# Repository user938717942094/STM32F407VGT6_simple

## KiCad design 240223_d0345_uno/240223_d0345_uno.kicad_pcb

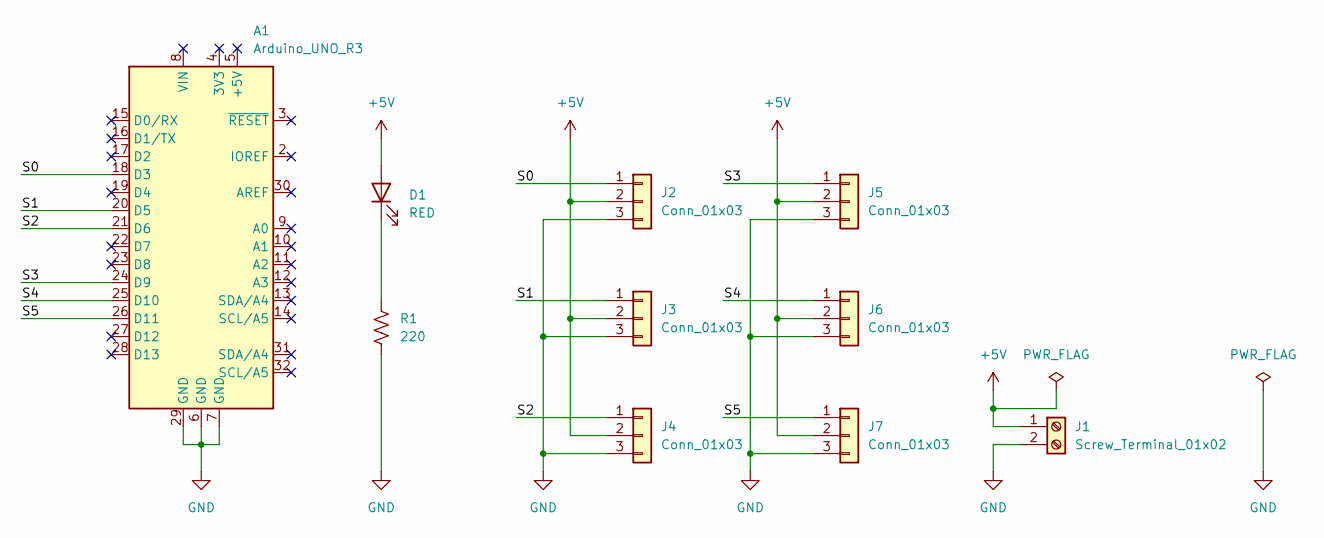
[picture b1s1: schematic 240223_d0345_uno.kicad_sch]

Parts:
A1: Arduino_UNO_R3
D1: RED; LED_D5.0mm
J1: Screw_Terminal_01x02; TerminalBlock_Phoenix_MKDS-1,5-2_1x02_P5.00mm_Horizontal
J2, J3, J4, J5, J6, J7: Conn_01x03; PinHeader_1x03_P2.54mm_Vertical
R1: 220; C_Disc_D5.0mm_W2.5mm_P5.00mm

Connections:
+5V: D1.2 (A), J1.1, J2.2, J3.2, J4.2, J5.2, J6.2, J7.2
/S0: A1.18 (D3), J2.1
/S1: A1.20 (D5), J3.1
/S2: A1.21 (D6), J4.1
/S3: A1.24 (D9), J5.1
/S4: A1.25 (D10), J6.1
/S5: A1.26 (D11), J7.1
GND: A1.6 (GND), A1.7 (GND), A1.29 (GND), J1.2, J2.3, J3.3, J4.3, J5.3, J6.3, J7.3, R1.2
unnamed: D1.1 (K), R1.1

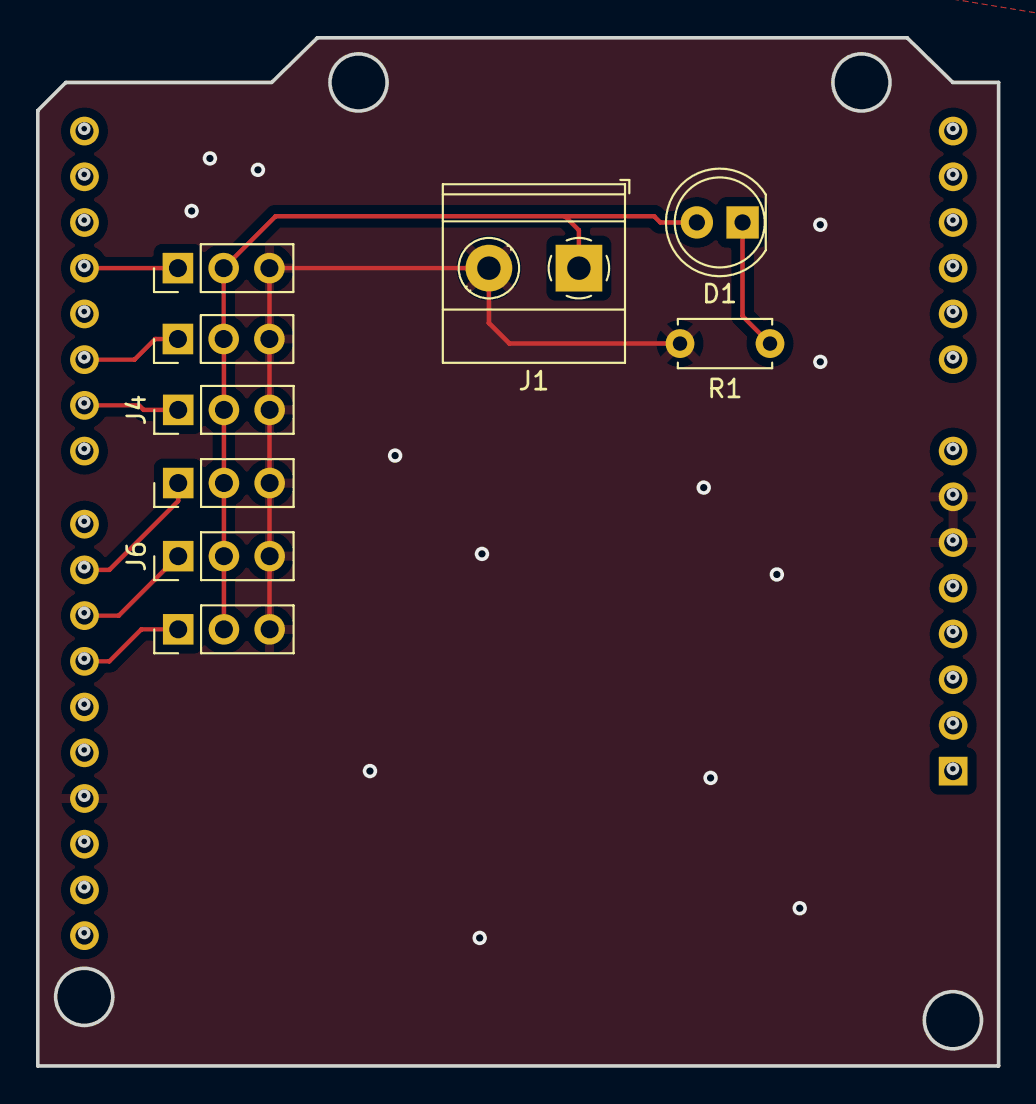
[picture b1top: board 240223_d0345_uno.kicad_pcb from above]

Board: 2 copper layers, 53.4 x 57.1 mm, 10 parts (1 on the bottom side), 9 nets.

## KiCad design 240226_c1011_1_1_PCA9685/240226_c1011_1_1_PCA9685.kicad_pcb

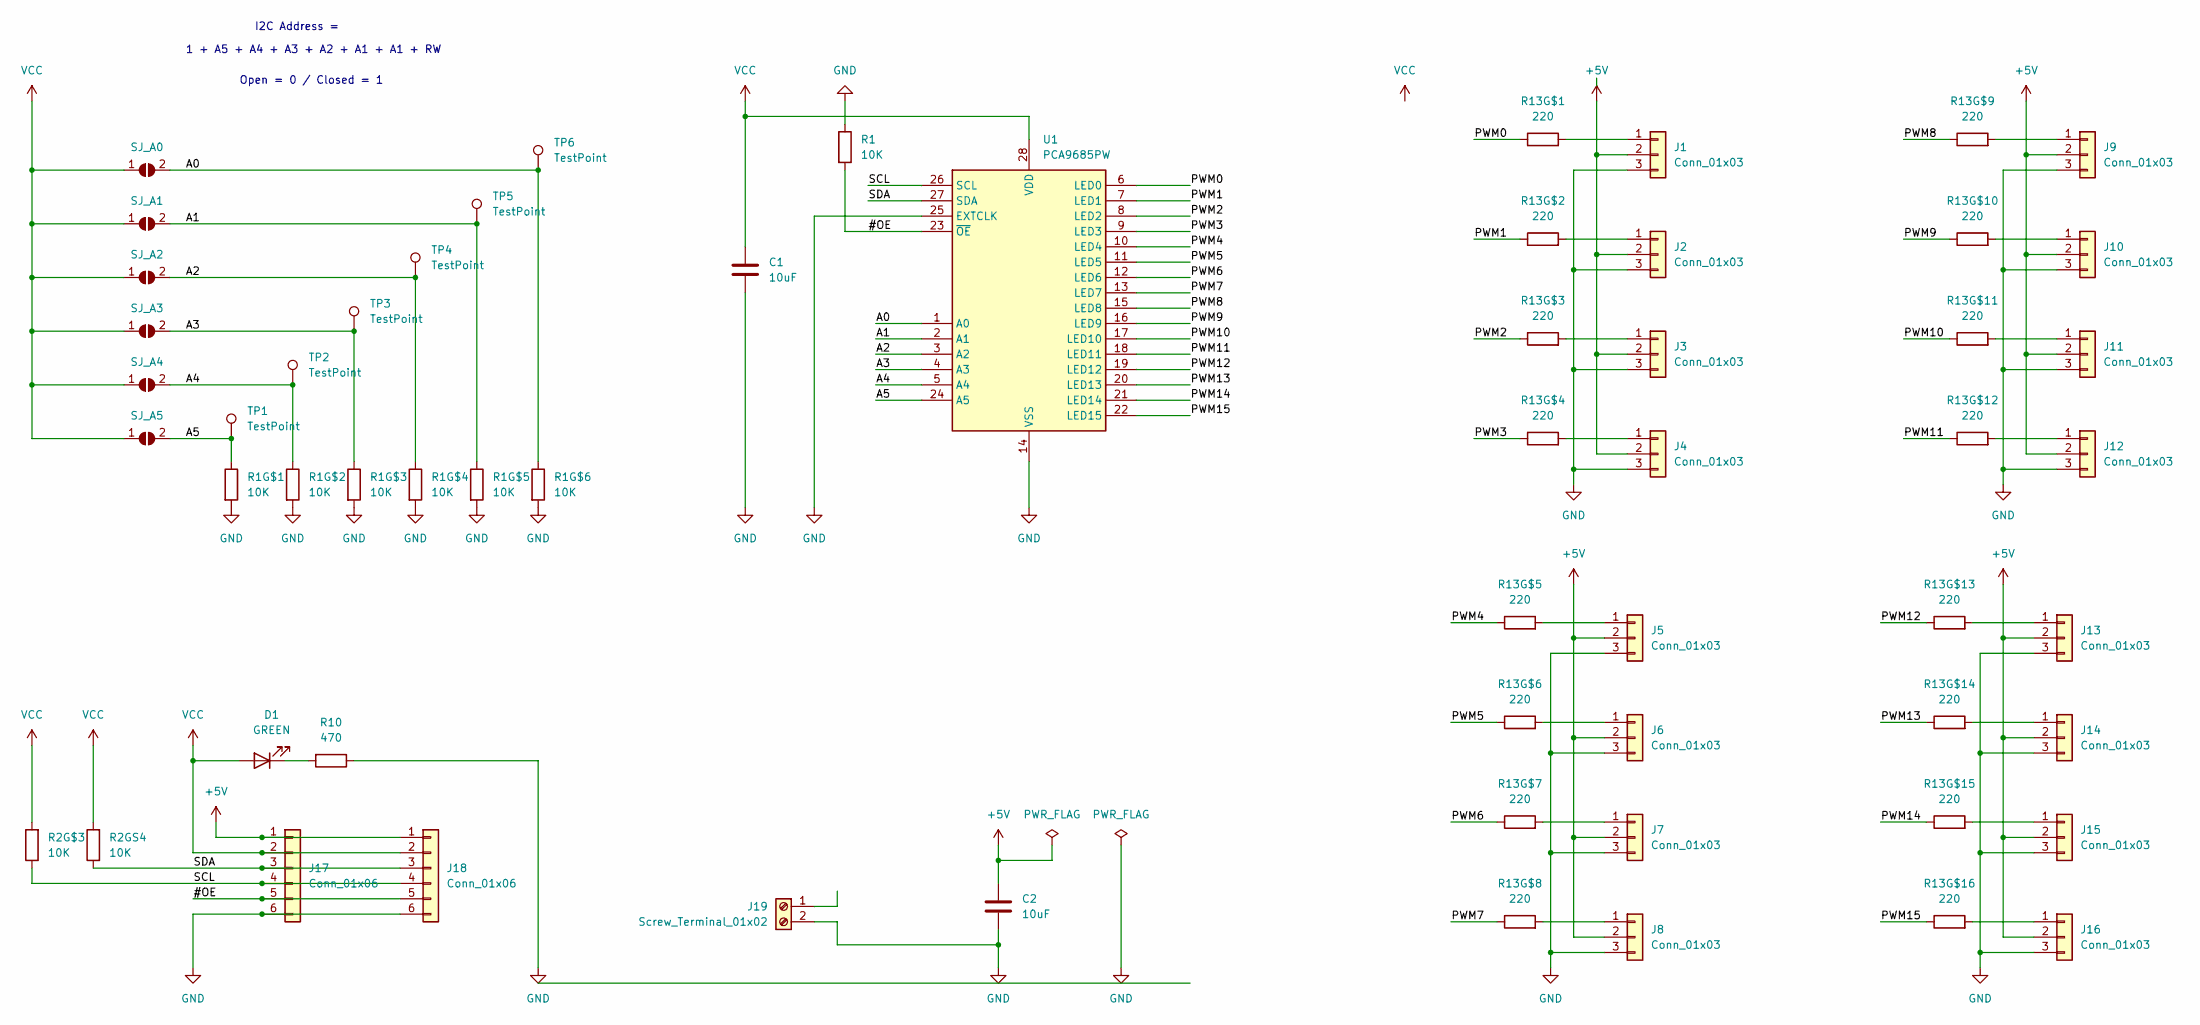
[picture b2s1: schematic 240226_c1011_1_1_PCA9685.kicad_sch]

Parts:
C1, C2: 10uF
D1: GREEN
J1, J2, J3, J4, J5, J6, J7, J8, J9, J10, J11, J12, J13, J14, J15, J16: Conn_01x03; PinHeader_1x03_P2.54mm_Vertical
J17, J18: Conn_01x06
J19: Screw_Terminal_01x02; TerminalBlock_Phoenix_MKDS-1,5-2_1x02_P5.00mm_Horizontal
JP1: SJ_A0
JP2: SJ_A1
JP3: SJ_A2
JP4: SJ_A3
JP5: SJ_A4
JP6: SJ_A5
R1, R1G$1, R1G$2, R1G$3, R1G$4, R1G$5, R1G$6, R2G$3, R2GS4: 10K
R10: 470
R13G$1, R13G$2, R13G$3, R13G$4, R13G$5, R13G$6, R13G$7, R13G$8, R13G$9, R13G$10, R13G$11, R13G$12, R13G$13, R13G$14, R13G$15, R13G$16: 220
TP1, TP2, TP3, TP4, TP5, TP6: TestPoint
U1: PCA9685PW; TSSOP-28_4.4x9.7mm_P0.65mm

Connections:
+5V: C2.1, J1.2, J2.2, J3.2, J4.2, J5.2, J6.2, J7.2, J8.2, J9.2, J10.2, J11.2, J12.2, J13.2, J14.2, J15.2, J16.2, J17.1, J18.1; also elsewhere on the board
/#OE: J17.5, J18.5, R1.2, U1.23 (~OE)
/A0: JP1.2 (B), R1G$6.1, TP6.1, U1.1 (A0); also elsewhere on the board
/A1: JP2.2 (B), R1G$5.1, TP5.1, U1.2 (A1); also elsewhere on the board
/A2: JP3.2 (B), R1G$4.1, TP4.1, U1.3 (A2); also elsewhere on the board
/A3: JP4.2 (B), R1G$3.1, TP3.1, U1.4 (A3); also elsewhere on the board
/A4: JP5.2 (B), R1G$2.1, TP2.1, U1.5 (A4); also elsewhere on the board
/A5: JP6.2 (B), R1G$1.1, TP1.1, U1.24 (A5); also elsewhere on the board
/PWM0: R13G$1.1, U1.6 (LED0)
/PWM1: R13G$2.1, U1.7 (LED1)
/PWM2: R13G$3.1, U1.8 (LED2)
/PWM3: R13G$4.1, U1.9 (LED3)
/PWM4: R13G$5.1, U1.10 (LED4)
/PWM5: R13G$6.1, U1.11 (LED5)
/PWM6: R13G$7.1, U1.12 (LED6)
/PWM7: R13G$8.1, U1.13 (LED7)
/PWM8: R13G$9.1, U1.15 (LED8)
/PWM9: R13G$10.1, U1.16 (LED9)
/PWM10: R13G$11.1, U1.17 (LED10)
/PWM11: R13G$12.1, U1.18 (LED11)
/PWM12: R13G$13.1, U1.19 (LED12)
/PWM13: R13G$14.1, U1.20 (LED13)
/PWM14: R13G$15.1, U1.21 (LED14)
/PWM15: R13G$16.1, U1.22 (LED15)
/SCL: J17.4, J18.4, R2G$3.1, U1.26 (SCL); also elsewhere on the board
/SDA: J17.3, J18.3, R2GS4.1, U1.27 (SDA); also elsewhere on the board
GND: C1.2, C2.2, J1.3, J2.3, J3.3, J4.3, J5.3, J6.3, J7.3, J8.3, J9.3, J10.3, J11.3, J12.3, J13.3, J14.3, J15.3, J16.3, J17.6, J18.6, J19.2, R1.1, R1G$1.2, R1G$2.2, R1G$3.2, R1G$4.2, R1G$5.2, R1G$6.2, R10.1, U1.14 (VSS), U1.25 (EXTCLK); also elsewhere on the board
unnamed: D1.1 (K), R10.2
unnamed: J1.1, R13G$1.2
unnamed: J2.1, R13G$2.2
unnamed: J3.1, R13G$3.2
unnamed: J4.1, R13G$4.2
unnamed: J5.1, R13G$5.2
unnamed: J6.1, R13G$6.2
unnamed: J7.1, R13G$7.2
unnamed: J8.1, R13G$8.2
unnamed: J9.1, R13G$9.2
unnamed: J10.1, R13G$10.2
unnamed: J11.1, R13G$11.2
unnamed: J12.1, R13G$12.2
unnamed: J13.1, R13G$13.2
unnamed: J14.1, R13G$14.2
unnamed: J15.1, R13G$15.2
unnamed: J16.1, R13G$16.2
VCC: C1.1, D1.2 (A), J17.2, J18.2, J19.1, JP1.1 (A), JP2.1 (A), JP3.1 (A), JP4.1 (A), JP5.1 (A), JP6.1 (A), R2G$3.2, R2GS4.2, U1.28 (VDD); also elsewhere on the board

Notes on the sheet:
1 + A5 + A4 + A3 + A2 + A1 + A1 + RW
Open = 0 / Closed = 1
I2C Address =

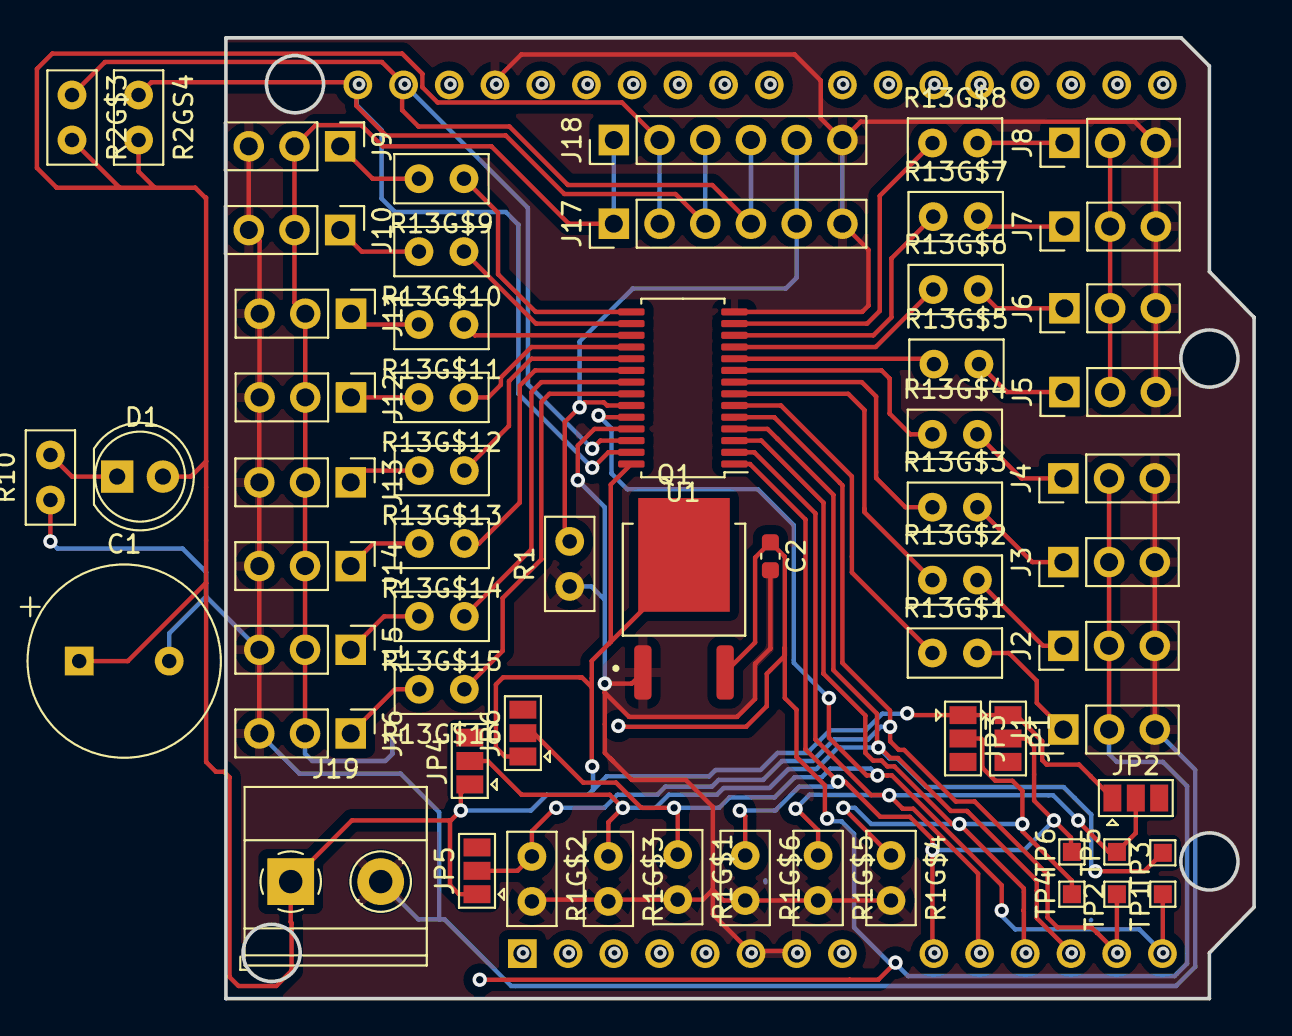
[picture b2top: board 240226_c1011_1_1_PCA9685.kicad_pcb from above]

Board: 2 copper layers, 57.1 x 53.4 mm, 63 parts (1 on the bottom side), 45 nets.

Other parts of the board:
A1: Arduino_UNO_R3
Q1: AOD417; DPAK228P994X240_3N

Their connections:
+5V: Q1.3; also elsewhere on the board
/A0: A1.9 (A0); also elsewhere on the board
/A1: A1.10 (A1); also elsewhere on the board
/A2: A1.11 (A2); also elsewhere on the board
/A3: A1.12 (A3); also elsewhere on the board
/A4: A1.13 (SDA/A4); also elsewhere on the board
/A5: A1.14 (SCL/A5); also elsewhere on the board
/SCL: A1.31 (SDA/A4); also elsewhere on the board
/SDA: A1.32 (SCL/A5); also elsewhere on the board
GND: A1.6 (GND), A1.7 (GND), A1.29 (GND), Q1.1; also elsewhere on the board
VCC: Q1.4; also elsewhere on the board

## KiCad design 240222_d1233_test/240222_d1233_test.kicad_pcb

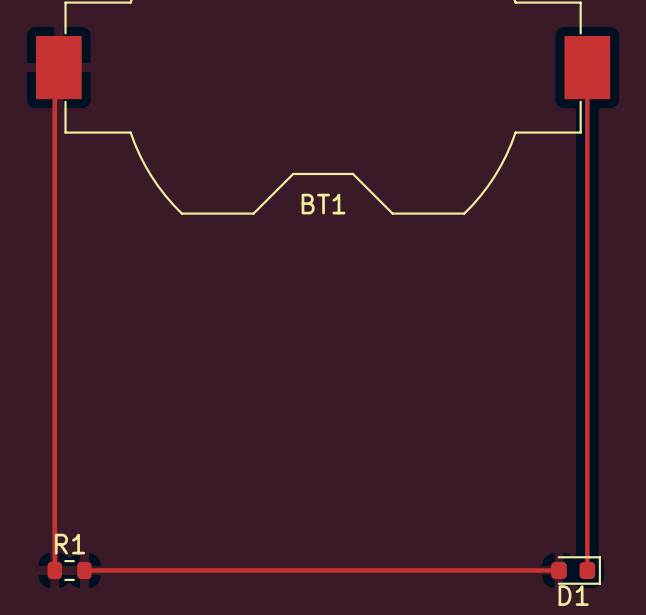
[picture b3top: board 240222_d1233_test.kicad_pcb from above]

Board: 2 copper layers, 3 parts (0 on the bottom side), 2 nets.

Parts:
BT1: Battery_Cell; BatteryHolder_Keystone_1058_1x2032
D1: 20mA; D_0603_1608Metric
R1: 1k; R_0603_1608Metric

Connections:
+5V: BT1.1 (+), D1.2 (A), R1.1, R1.2
GND: BT1.2 (-), D1.1 (K)

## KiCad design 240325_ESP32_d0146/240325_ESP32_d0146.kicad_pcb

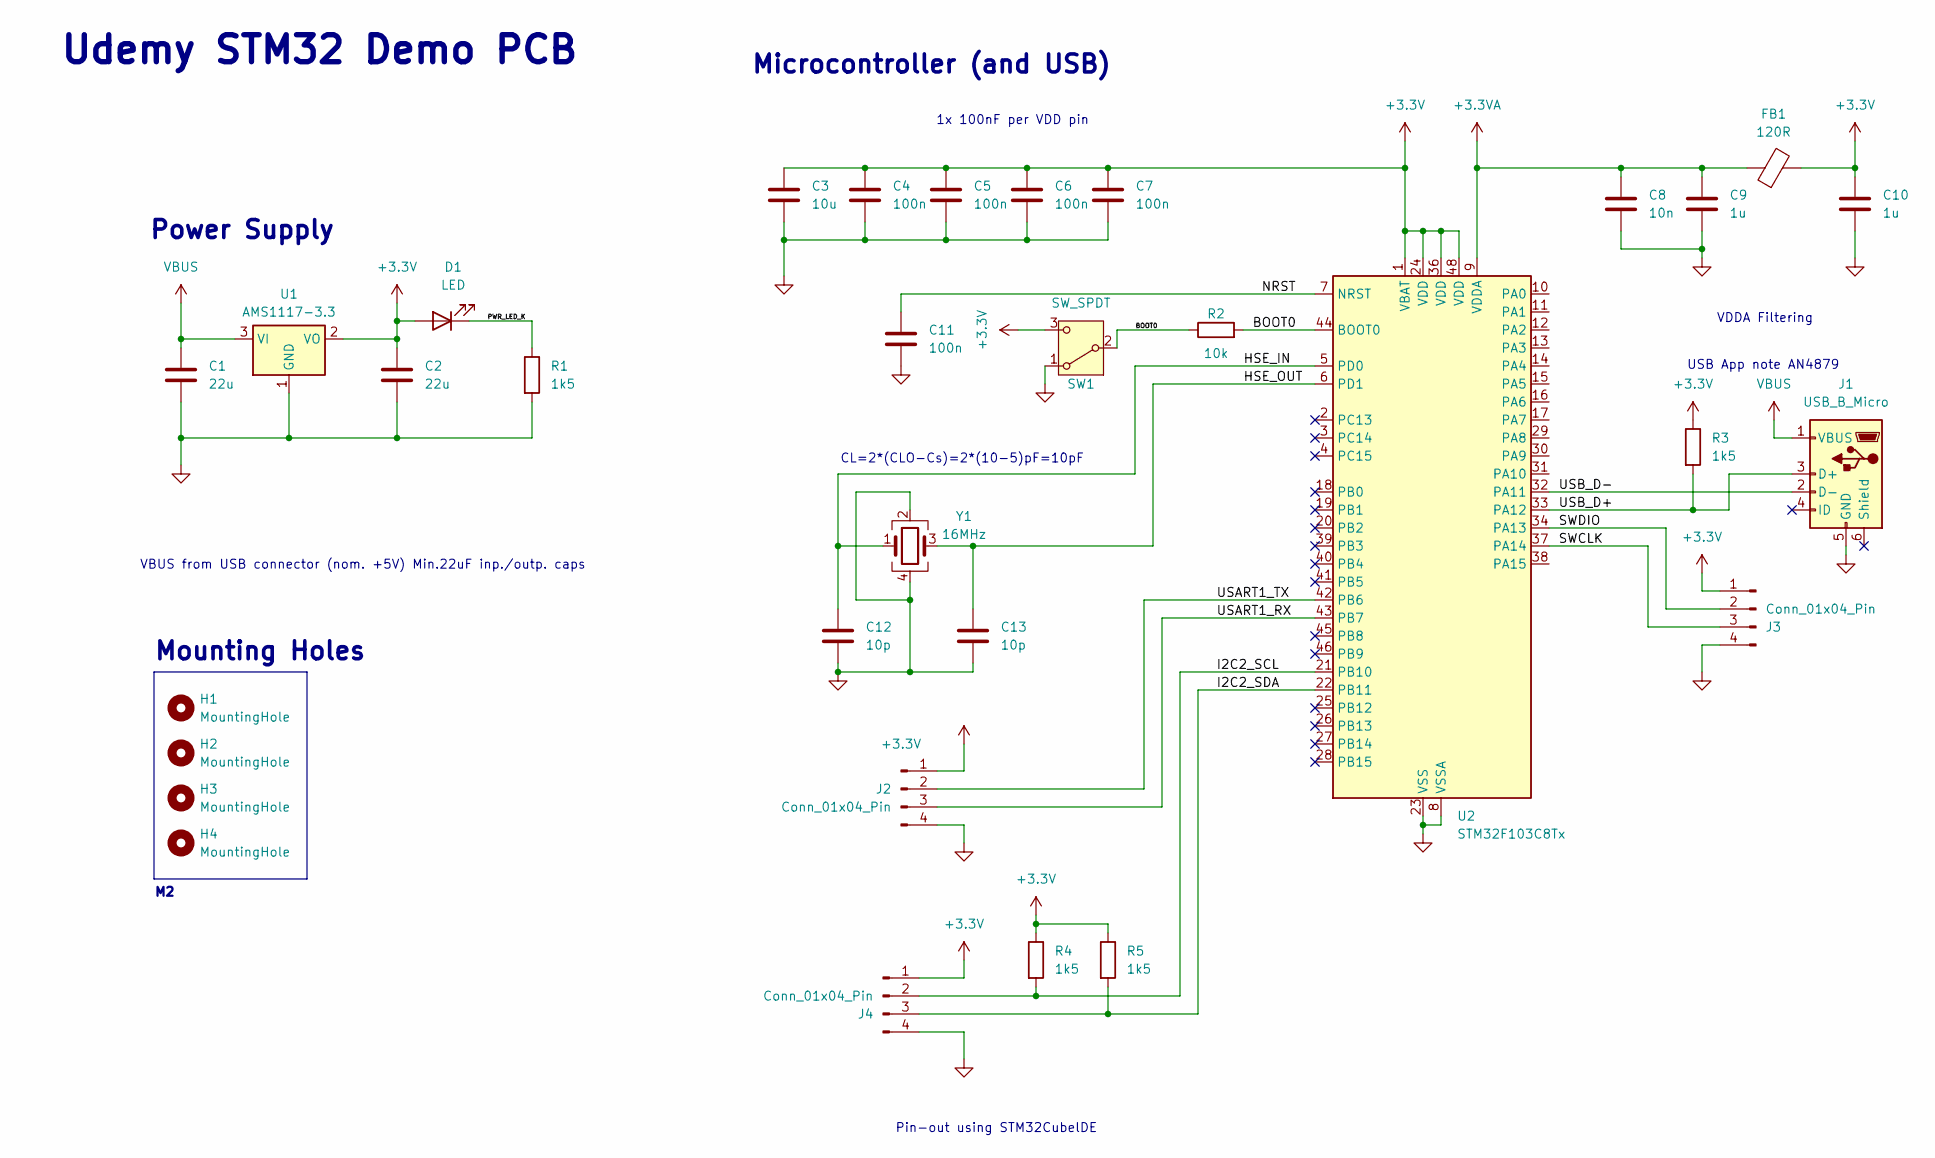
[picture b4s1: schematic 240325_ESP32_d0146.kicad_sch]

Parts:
C1, C2: 22u; C_0805_2012Metric
C3: 10u; C_0603_1608Metric
C4, C5, C6, C7, C11: 100n; C_0402_1005Metric
C8: 10n; C_0402_1005Metric
C9, C10: 1u; C_0402_1005Metric
C12, C13: 10p; C_0402_1005Metric
D1: LED; LED_0603_1608Metric
FB1: 120R; L_0603_1608Metric
H1, H2, H3, H4: MountingHole; MountingHole_2.1mm
J1: USB_B_Micro; USB_Micro-B_Wuerth_629105150521
J2, J3, J4: Conn_01x04_Pin; PinHeader_1x04_P2.54mm_Vertical
R1, R3, R4, R5: 1k5; R_0402_1005Metric
R2: 10k; R_0402_1005Metric
SW1: SW_SPDT; SW_SPDT_PCM12
U1: AMS1117-3.3; SOT-223-3_TabPin2
U2: STM32F103C8Tx; LQFP-48_7x7mm_P0.5mm
Y1: 16MHz; Crystal_SMD_3225-4Pin_3.2x2.5mm

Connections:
+3.3V: C2.1, C3.1, C4.1, C5.1, C6.1, C7.1, C10.1, D1.2 (A), FB1.2, J2.1, J3.1, J4.1, R3.1, R4.1, R5.1, SW1.3 (C), U1.2 (VO), U2.1 (VBAT), U2.24 (VDD), U2.36 (VDD), U2.48 (VDD)
+3.3VA: C8.1, C9.1, FB1.1, U2.9 (VDDA)
/BOOT0: R2.1, R2.2, SW1.2 (B), U2.44 (BOOT0)
/HSE_IN: C12.1, U2.5 (PD0), Y1.1
/HSE_OUT: C13.1, U2.6 (PD1), Y1.3
/I2C2_SCL: J4.2, R4.2, U2.21 (PB10)
/I2C2_SDA: J4.3, R5.2, U2.22 (PB11)
/NRST: C11.1, U2.7 (NRST)
/PWR_LED_K: D1.1 (K), R1.1
/SWCLK: J3.3, U2.37 (PA14)
/SWDIO: J3.2, U2.34 (PA13)
/USART1_RX: J2.3, U2.43 (PB7)
/USART1_TX: J2.2, U2.42 (PB6)
/USB_D+: J1.3 (D+), R3.2, U2.33 (PA12)
/USB_D-: J1.2 (D-), U2.32 (PA11)
GND: C1.2, C2.2, C3.2, C4.2, C5.2, C6.2, C7.2, C8.2, C9.2, C10.2, C11.2, C12.2, C13.2, J1.5 (GND), J2.4, J3.4, J4.4, R1.2, SW1.1 (A), U1.1 (GND), U2.8 (VSSA), U2.23 (VSS), U2.35 (VSS), U2.47 (VSS), Y1.2, Y1.4
VBUS: C1.1, J1.1 (VBUS), U1.3 (VI)

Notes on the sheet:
Pin-out using STM32CubelDE
Microcontroller (and USB)
Mounting Holes
Power Supply
CL=2*(CLO-Cs)=2*(10-5)pF=10pF
VBUS from USB connector (nom. +5V) Min.22uF inp./outp. caps
1x 100nF per VDD pin
Udemy STM32 Demo PCB
USB App note AN4879
VDDA Filtering

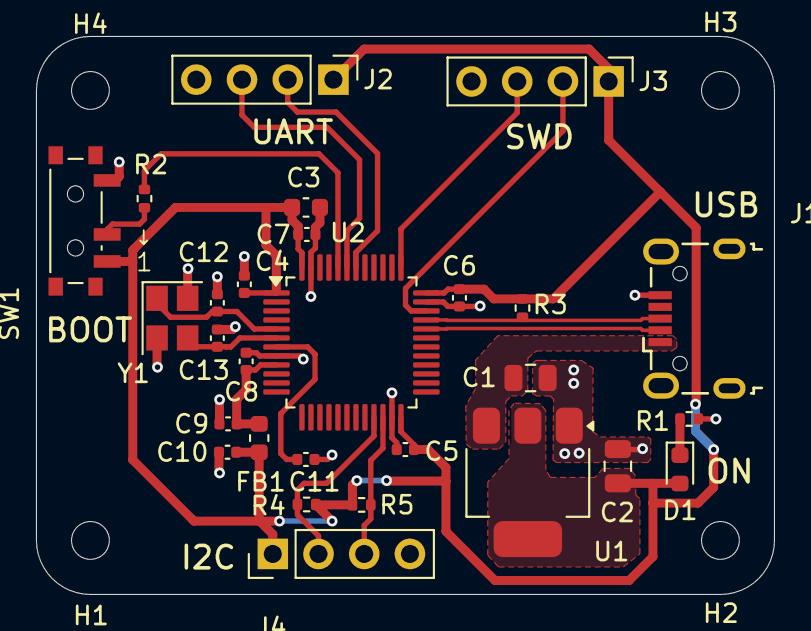
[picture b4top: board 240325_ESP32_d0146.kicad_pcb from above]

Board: 2 copper layers, 41.0 x 31.0 mm, 32 parts (0 on the bottom side), 17 nets.
